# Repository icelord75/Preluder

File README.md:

# Prelude ExtraGuages and Odometer

Secondary VFD dashboard display and Dot matrix LED display replacement for mechanical odometer in Honda Prelude IV

## Supported modes:

 - Arduino Mega2561 controller
 - OLED mode and values display with dimming feature
 - Voltmeter
 - Oil pressure (VDO) / Oil temperature (NTC)
 - AirFuelRatio sensor / EGT sensor
 - Contactless brakes temperature (PIR)
 - Alarm system
 - Precise configure wheel/VSS ratio
 - Total mileage
 - A/B trip (up to 9999.9km)
 - Motor hours counter
 - Configurable LED needle illumination with dimming feature
 - Configurable Electroluminescence instrumental cluster illumination controller
 - Outside Temperature (DS1820 sensor)

## License

**Prelude ExtraGuages and Odometer** is available under GPL License.

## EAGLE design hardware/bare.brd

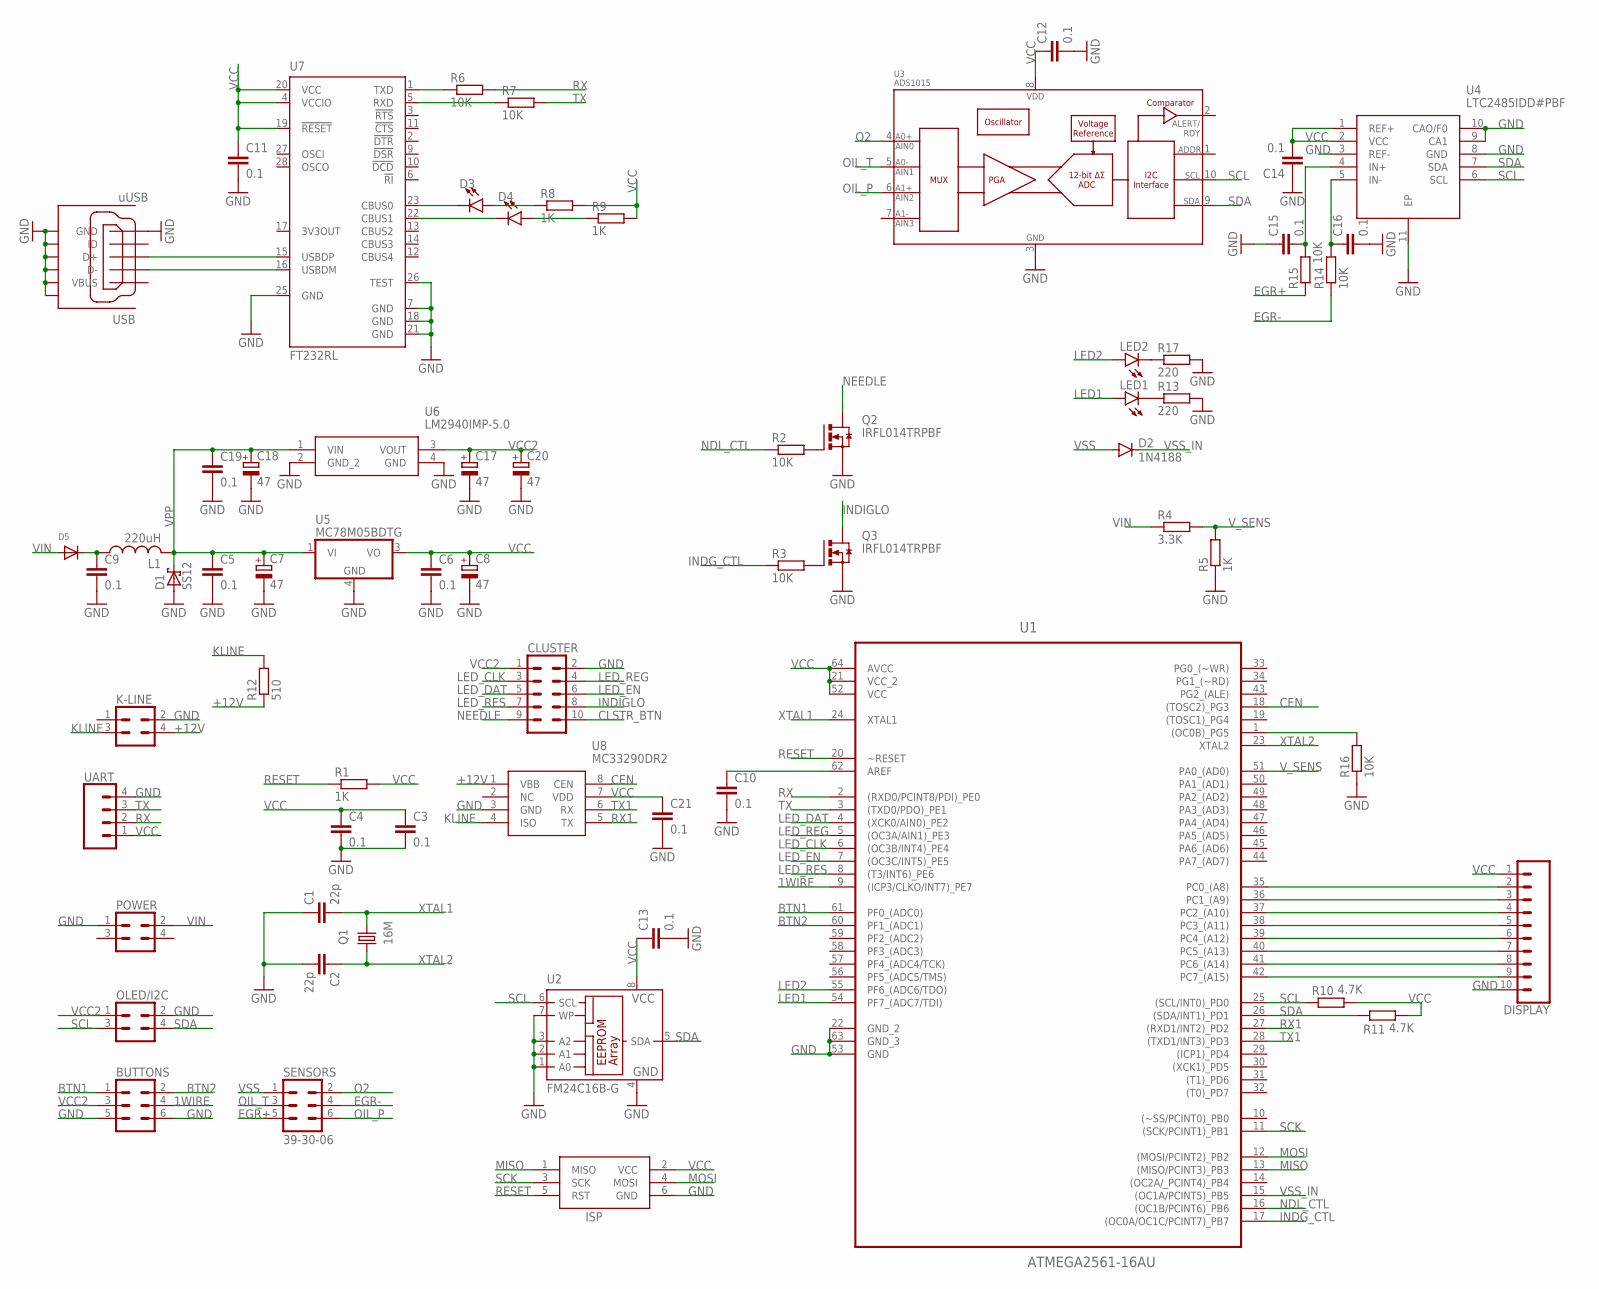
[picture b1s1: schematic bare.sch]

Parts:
BUTTONS: 39-30-06; 39-30-?06?
C1, C2: 22p; C0603K
C3, C4, C10, C11, C13, C14, C15, C16, C21: 0.1; C0603K
C5, C6, C9, C12, C19: 0.1; C0805K
C7, C8, C17, C18, C20: 47; SMC_C
CLUSTER: 39-30-10; 39-30-?10?
D1: SS12; SOD80C
D2: 1N4188; SOD-323
D3: GREEN; LED-0603
D4: RED; LED-0603
D5: DIODESMA; SMADIODE
DISPLAY: CONN_10"; 1X10
ISP: AVRISP-6; AVRISP
K-LINE: 39-30-04; 39-30-?04?
L1: 220uH; PIS2816
LED1, LED2: LEDCHIP-LED0805; CHIP-LED0805
OLED/I2C: 39-30-04; 39-30-?04?
POWER: 39-30-04; 39-30-?04?
Q1: 16M; 3.2X2.5_KX-7
Q2, Q3: IRFL014TRPBF; SOT223
R1, R5, R8, R9: 1K; R0603
R2, R3, R6, R7, R14, R15, R16: 10K; R0603
R4: 3.3K; R0603
R10, R11: 4.7K; R0603
R12: 510; R0603
R13, R17: 220; R0603
SENSORS: 39-30-06; 39-30-?06?
U1: ATMEGA2561-16AU; QFP80P1600X1600X120-64N
U2: FM24C16B-G; SO-08
U3: ADS1015; MSOP10
U4: LTC2485IDD#PBF; SON50P300X300X80-11N
U5: MC78M05BDTG; DPACK_3
U6: LM2940IMP-5.0; SOT230P696X180-4N
U7: FT232RL; SSOP28
U8: MC33290DR2; SOIC127P600X175-8N
UART: UART; 1X04
USB: uUSB; GHI-CONNECTORS_10118192-0001LF(MICRO-USB-B-AMPHENOL-FCI)

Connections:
1WIRE: BUTTONS.4, U1.9 ((ICP3/CLKO/INT7)_PE7)
+12V: K-LINE.4, R12.1, U8.1 (VBB)
BTN1: BUTTONS.1, U1.61 (PF0_(ADC0))
BTN2: BUTTONS.2, U1.60 (PF1_(ADC1))
CEN: U1.18 ((TOSC2)_PG3), U8.8 (CEN)
CLSTR_BTN: CLUSTER.10, R16.2, U1.1 ((OC0B)_PG5)
EGR+: R15.1, SENSORS.5
EGR-: R14.1, SENSORS.4
GND: BUTTONS.5, BUTTONS.6, C1.1, C2.2, C3.2, C4.2, C5.2, C6.2, C7.-, C8.-, C9.2, C10.2, C11.2, C12.2, C13.2, C14.1, C15.1, C16.2, C17.-, C18.-, C19.2, C20.-, C21.2, CLUSTER.2, D1.2 (A), DISPLAY.10, ISP.6 (GND), K-LINE.2, OLED/I2C.2, POWER.1, Q2.3 (S), Q3.3 (S), R5.1, R13.2, R16.1, R17.2, U1.22 (GND_2), U1.53 (GND), U1.63 (GND_3), U2.1 (A0), U2.2 (A1), U2.3 (A2), U2.4 (GND), U2.7 (WP), U3.3 (VSS), U4.3 (REF-), U4.8 (GND), U4.9 (CA1), U4.10 (CAO/F0), U4.11 (EP), U5.4 (GND), U6.2 (GND_2), U6.4 (GND), U7.7 (GND), U7.18 (GND), U7.21 (GND), U7.25 (GND), U7.26 (TEST), U8.3 (GND), UART.4, USB.CGND1 (SGND1), USB.CGND2 (SGND2), USB.CGND3 (SGND3), USB.CGND4 (SGND4), USB.CGND5 (SGND5), USB.CGND6 (SGND6), USB.GND
INDG_CTL: R3.1, U1.17 ((OC0A/OC1C/PCINT7)_PB7)
INDIGLO: CLUSTER.8, Q3.2 (D), Q3.4 (D)
KLINE: K-LINE.3, R12.2, U8.4 (ISO)
LED1: LED1.A, U1.54 (PF7_(ADC7/TDI))
LED2: LED2.A, U1.55 (PF6_(ADC6/TDO))
LED_CLK: CLUSTER.3, U1.6 ((OC3B/INT4)_PE4)
LED_DAT: CLUSTER.5, U1.4 ((XCK0/AIN0)_PE2)
LED_EN: CLUSTER.6, U1.7 ((OC3C/INT5)_PE5)
LED_REG: CLUSTER.4, U1.5 ((OC3A/AIN1)_PE3)
LED_RES: CLUSTER.7, U1.8 ((T3/INT6)_PE6)
MISO: ISP.1 (MISO), U1.13 ((MISO/PCINT3)_PB3)
MOSI: ISP.4 (MOSI), U1.12 ((MOSI/PCINT2)_PB2)
unnamed: Q2.1 (G), R2.2
unnamed: Q3.1 (G), R3.2
unnamed: C10.1, U1.62 (AREF)
unnamed: R6.1, U7.1 (TXD)
unnamed: R7.1, U7.5 (RXD)
unnamed: U7.15 (USBDP), USB.D+
unnamed: U7.16 (USBDM), USB.D-
unnamed: D3.C, U7.23 (CBUS0)
unnamed: D4.C, U7.22 (CBUS1)
unnamed: D3.A, R8.1
unnamed: D4.A, R9.1
unnamed: LED1.C, R13.1
unnamed: LED2.C, R17.1
unnamed: C9.1, D5.C, L1.1
unnamed: DISPLAY.9, U1.42 (PC7_(A15))
unnamed: C16.1, R14.2, U4.5 (IN-)
unnamed: C15.2, R15.2, U4.4 (IN+)
unnamed: DISPLAY.8, U1.41 (PC6_(A14))
unnamed: DISPLAY.7, U1.40 (PC5_(A13))
unnamed: DISPLAY.6, U1.39 (PC4_(A12))
unnamed: DISPLAY.5, U1.38 (PC3_(A11))
unnamed: DISPLAY.4, U1.37 (PC2_(A10))
unnamed: DISPLAY.3, U1.36 (PC1_(A9))
unnamed: DISPLAY.2, U1.35 (PC0_(A8))
NDL_CTL: R2.1, U1.16 ((OC1B/PCINT6)_PB6)
NEEDLE: CLUSTER.9, Q2.2 (D), Q2.4 (D)
O2: SENSORS.2, U3.4 (AIN0)
OIL_P: SENSORS.6, U3.6 (AIN2)
OIL_T: SENSORS.3, U3.5 (AIN1)
RESET: ISP.5 (RST), R1.1, U1.20 (~RESET)
RX: R6.2, U1.2 ((RXD0/PCINT8/PDI)_PE0), UART.2
RX1: U1.27 ((RXD1/INT2)_PD2), U8.5 (TX)
SCK: ISP.3 (SCK), U1.11 ((SCK/PCINT1)_PB1)
SCL: OLED/I2C.3, R10.1, U1.25 ((SCL/INT0)_PD0), U2.6 (SCL), U3.10 (SCL), U4.6 (SCL)
SDA: OLED/I2C.4, R11.1, U1.26 ((SDA/INT1)_PD1), U2.5 (SDA), U3.9 (SDA), U4.7 (SDA)
TX: R7.2, U1.3 ((TXD0/PDO)_PE1), UART.3
TX1: U1.28 ((TXD1/INT3)_PD3), U8.6 (RX)
VCC: C3.1, C4.1, C6.1, C8.+, C11.1, C12.1, C13.1, C14.2, C21.1, DISPLAY.1, ISP.2 (VCC), R1.2, R8.2, R9.2, R10.2, R11.2, U1.21 (VCC_2), U1.52 (VCC), U1.64 (AVCC), U2.8 (VCC), U3.8 (VDD), U4.1 (REF+), U4.2 (VCC), U5.3 (VO), U7.4 (VCCIO), U7.19 (!RESET), U7.20 (VCC), U8.7 (VDD), UART.1
VCC2: BUTTONS.3, C17.+, C20.+, CLUSTER.1, OLED/I2C.1, U6.3 (VOUT)
VIN: D5.A, POWER.2, R4.1
VPP: C5.1, C7.+, C18.+, C19.1, D1.1 (K), L1.2, U5.1 (VI), U6.1 (VIN)
VSS: D2.A, SENSORS.1
VSS_IN: D2.C, U1.15 ((OC1A/PCINT5)_PB5)
V_SENS: R4.2, R5.2, U1.51 (PA0_(AD0))
XTAL1: C1.2, Q1.3 (2), U1.24 (XTAL1)
XTAL2: C2.1, Q1.1, U1.23 (XTAL2)

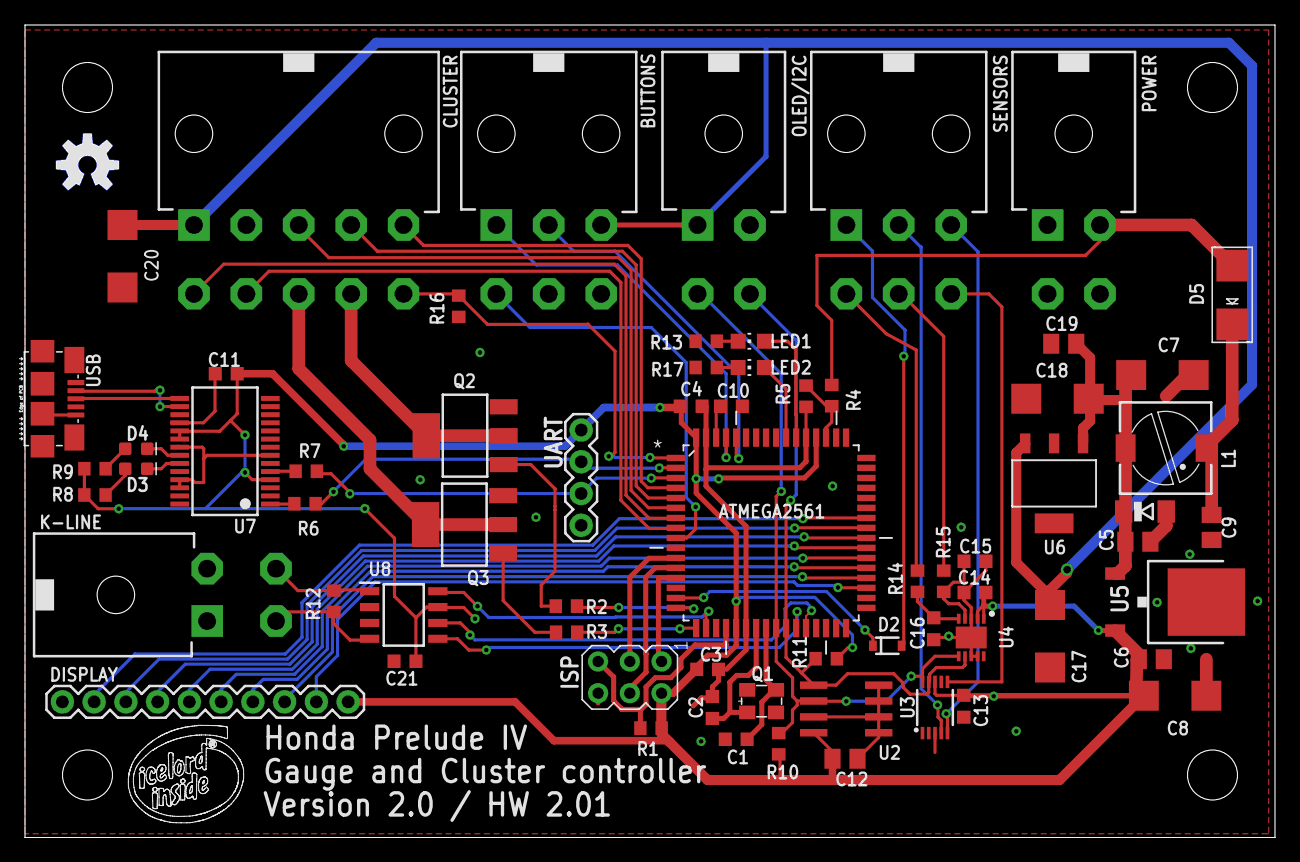
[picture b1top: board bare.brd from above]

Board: 2 copper layers, 100.0 x 65.0 mm, 70 parts (1 on the bottom side), 67 nets.

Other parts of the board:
U$1: ICELORD_SMALL
U$2: OSHW-LOGO-M
U$3: OSHW-LOGO-M_COPPER

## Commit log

2019-03-25 initial
2019-03-27 check git mirror
2019-04-04 schematics
2019-04-10 odomenter board init

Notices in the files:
parts and their libraries:
crystal-geyer_V1_0: Copyright: Geyer-Electronic
SparkFun-Connectors: Licensing: Creative Commons ShareAlike 4.0 International - https://creativecommons.org/licenses/by-sa/4.0
con-molex-mini-fit: Copyright (C) 2011, Bob Starr
